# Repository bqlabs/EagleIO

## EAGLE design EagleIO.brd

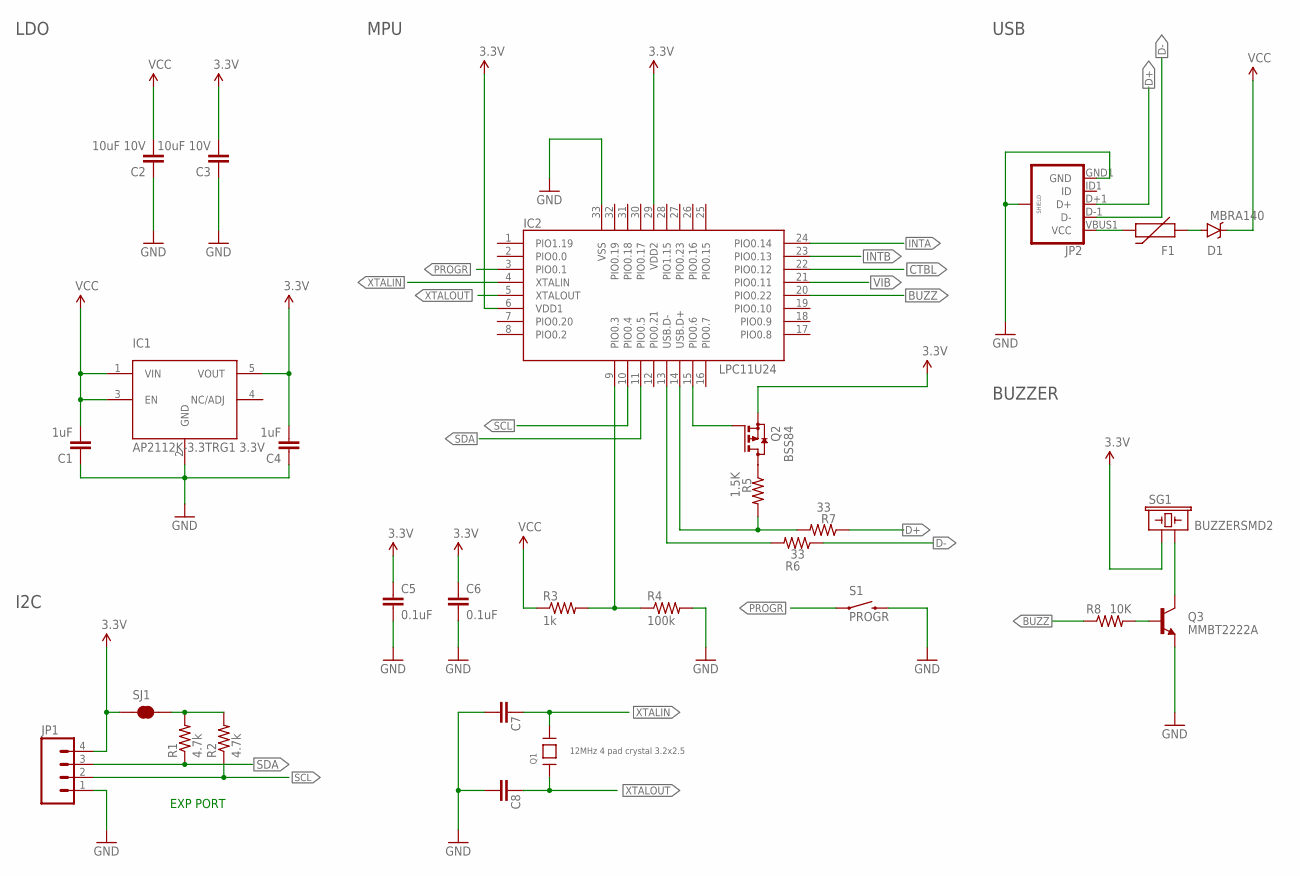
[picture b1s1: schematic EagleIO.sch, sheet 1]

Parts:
C1, C4: 1uF; 0402-CAP
C2, C3: 10uF 10V; 0402-CAP
C5, C6: 0.1uF; 0402-CAP
C7, C8: 27pF; 0402-CAP
D1: MBRA140; SMA-DIODE
F1: PTC0603; 0603
IC1: AP2112K-3.3TRG1 3.3V; SOT23-5
IC2: LPC11U24; HVQFN33_5X5MM
JP1: M04LONGPADS; 1X04_LONGPADS
JP2: USB_MICROB_PLUGCONN-11752; USB-B-MICRO-SMD_V03
Q1: 12MHz 4 pad crystal 3.2x2.5; CRYSTAL_3.2X2.5
Q2: BSS84; SOT23
Q3: MMBT2222A; SOT23-3
R1, R2: 4.7k; 0402-RES
R3: 1k; 0402-RES
R4: 100k; 0402-RES
R5: 1.5K; 0402-RES
R6, R7: 33; 0402-RES
R8: 10K; 0402-RES
S1: PROGR; TACTILE-SWITCH-1101NE
SG1: BUZZERSMD2; BUZZER-CCV
SJ1: JUMPER-PAD-2-NC_BY_TRACE; PAD-JUMPER-2-NC_BY_TRACE_YES_SILK

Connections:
3.3V: C3.2, C4.2, C5.1, C6.1, IC1.5 (VOUT), IC2.6 (VDD1), IC2.29 (VDD2), JP1.4, Q2.2 (S), SG1.+ (1), SJ1.1; also elsewhere on the board
BUZZ: IC2.20 (PIO0.22), R8.1
CTBL: IC2.22 (PIO0.12); also elsewhere on the board
D+: JP2.D+1 (D+), R7.1
D-: JP2.D-1 (D-), R6.1
GND: C1.1, C2.1, C3.1, C4.1, C5.2, C6.2, C7.2, C8.2, IC1.2 (GND), IC2.33 (VSS), JP1.1, JP2.GND1 (GND), JP2.SHIELD1 (SHIELD), JP2.SHIELD2 (SHIELD), JP2.SHIELD3 (SHIELD), Q3.2 (E), R4.2, S1.2; also elsewhere on the board
INTA: IC2.24 (PIO0.14); also elsewhere on the board
INTB: IC2.23 (PIO0.13); also elsewhere on the board
unnamed: D1.A, F1.1
unnamed: F1.2, JP2.VBUS1 (VCC)
unnamed: Q3.3 (C), SG1.- (2)
unnamed: Q3.1 (B), R8.2
unnamed: IC2.14 (USB.D+), R5.2, R7.2
unnamed: IC2.13 (USB.D-), R6.2
unnamed: Q2.3 (D), R5.1
unnamed: IC2.15 (PIO0.6), Q2.1 (G)
unnamed: R1.2, R2.2, SJ1.2
P0.3/ISP_COMMAND_USB_HIGH: IC2.9 (PIO0.3), R3.2, R4.1
PROGR: IC2.3 (PIO0.1), S1.1
SCL: IC2.10 (PIO0.4), JP1.2, R2.1; also elsewhere on the board
SDA: IC2.11 (PIO0.5), JP1.3, R1.1; also elsewhere on the board
VCC: C1.2, C2.2, D1.C, IC1.1 (VIN), IC1.3 (EN), R3.1; also elsewhere on the board
VIB: IC2.21 (PIO0.11); also elsewhere on the board
XTALIN: C7.1, IC2.4 (XTALIN), Q1.3
XTALOUT: C8.1, IC2.5 (XTALOUT), Q1.1

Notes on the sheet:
LDO
MPU
USB
I2C
BUZZER
EXP PORT

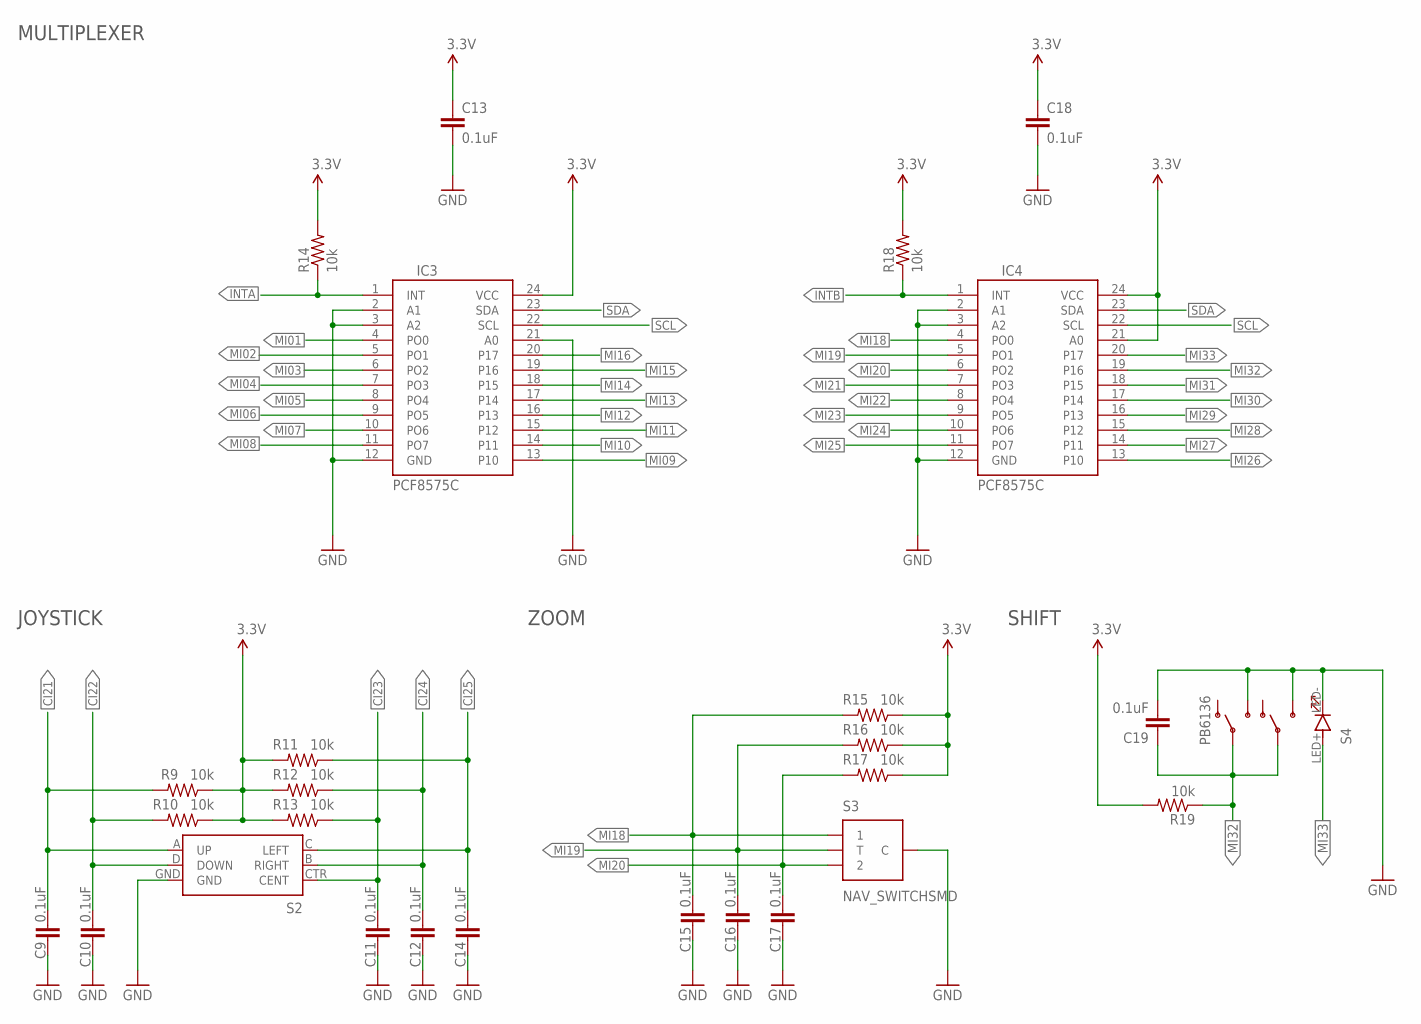
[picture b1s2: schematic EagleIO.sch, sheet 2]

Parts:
C9, C10, C11, C12, C13, C14, C15, C16, C17, C18, C19: 0.1uF; 0402-CAP
IC3, IC4: PCF8575C; SO-24DW
R9, R10, R11, R12, R13, R14, R15, R16, R17, R18, R19: 10k; 0402-RES
S2: JOYSTICK_MINI
S3: NAV_SWITCHSMD; NAV_SWITCH
S4: PB6136

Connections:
3.3V: C13.1, C18.1, IC3.24 (VCC), IC4.21 (A0), IC4.24 (VCC), R9.1, R10.1, R11.2, R12.2, R13.2, R14.2, R15.1, R16.1, R17.1, R18.2, R19.2; also elsewhere on the board
CI21: C9.2, R9.2, S2.A (UP); also elsewhere on the board
CI22: C10.2, R10.2, S2.D (DOWN); also elsewhere on the board
CI23: C11.2, R13.1, S2.CTR (CENT); also elsewhere on the board
CI24: C12.2, R12.1, S2.B (RIGHT); also elsewhere on the board
CI25: C14.2, R11.1, S2.C (LEFT); also elsewhere on the board
GND: C9.1, C10.1, C11.1, C12.1, C13.2, C14.1, C15.1, C16.1, C17.1, C18.2, C19.2, IC3.2 (A1), IC3.3 (A2), IC3.12 (GND), IC3.21 (A0), IC4.2 (A1), IC4.3 (A2), IC4.12 (GND), S2.GND, S3.C, S4.LED- (2), S4.NO1 (S), S4.NO2 (S1); also elsewhere on the board
INTA: IC3.1 (INT), R14.1; also elsewhere on the board
INTB: IC4.1 (INT), R18.1; also elsewhere on the board
MI01: IC3.4 (PO0); also elsewhere on the board
MI02: IC3.5 (PO1); also elsewhere on the board
MI03: IC3.6 (PO2); also elsewhere on the board
MI04: IC3.7 (PO3); also elsewhere on the board
MI05: IC3.8 (PO4); also elsewhere on the board
MI06: IC3.9 (PO5); also elsewhere on the board
MI07: IC3.10 (PO6); also elsewhere on the board
MI08: IC3.11 (PO7); also elsewhere on the board
MI09: IC3.13 (P10); also elsewhere on the board
MI10: IC3.14 (P11); also elsewhere on the board
MI11: IC3.15 (P12); also elsewhere on the board
MI12: IC3.16 (P13); also elsewhere on the board
MI13: IC3.17 (P14); also elsewhere on the board
MI14: IC3.18 (P15); also elsewhere on the board
MI15: IC3.19 (P16)
MI16: IC3.20 (P17)
MI18: C15.2, IC4.4 (PO0), R15.2, S3.1
MI19: C16.2, IC4.5 (PO1), R16.2, S3.T
MI20: C17.2, IC4.6 (PO2), R17.2, S3.2
MI21: IC4.7 (PO3); also elsewhere on the board
MI22: IC4.8 (PO4); also elsewhere on the board
MI23: IC4.9 (PO5); also elsewhere on the board
MI24: IC4.10 (PO6); also elsewhere on the board
MI25: IC4.11 (PO7); also elsewhere on the board
MI26: IC4.13 (P10); also elsewhere on the board
MI27: IC4.14 (P11); also elsewhere on the board
MI28: IC4.15 (P12); also elsewhere on the board
MI29: IC4.16 (P13)
MI30: IC4.17 (P14)
MI31: IC4.18 (P15)
MI32: C19.1, IC4.19 (P16), R19.1, S4.C1, S4.C2 (P1)
MI33: IC4.20 (P17), S4.LED+ (1)
SCL: IC3.22 (SCL), IC4.22 (SCL); also elsewhere on the board
SDA: IC3.23 (SDA), IC4.23 (SDA); also elsewhere on the board

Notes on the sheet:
MULTIPLEXER
JOYSTICK
ZOOM
SHIFT

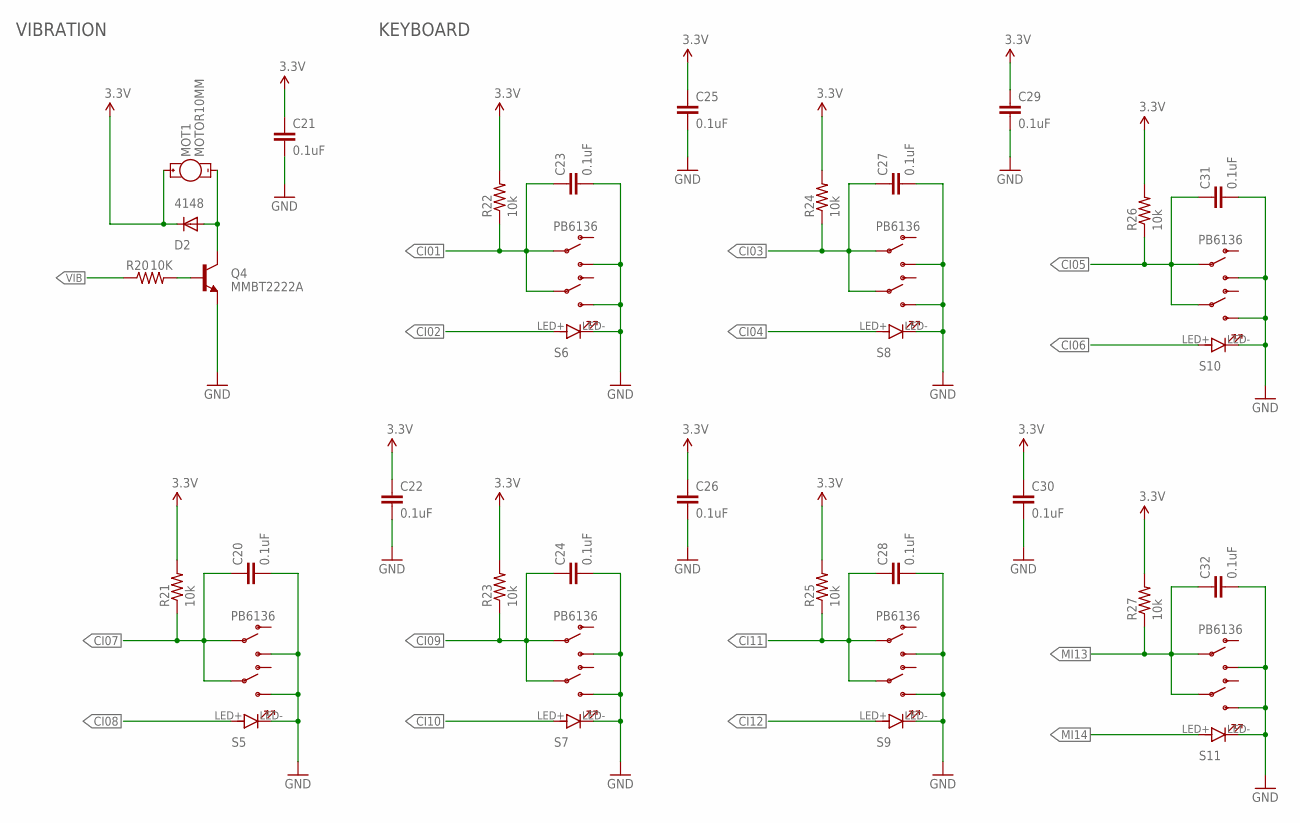
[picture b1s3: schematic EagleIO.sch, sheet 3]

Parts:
C20, C21, C22, C23, C24, C25, C26, C27, C28, C29, C30, C31, C32: 0.1uF; 0402-CAP
D2: 4148; MINIMELF
MOT1: MOTOR10MM; VIBE-MOTOR-10MM
Q4: MMBT2222A; SOT23-3
R20: 10K; 0402-RES
R21, R22, R23, R24, R25, R26, R27: 10k; 0402-RES
S5, S6, S7, S8, S9, S10, S11: PB6136

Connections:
3.3V: C21.1, C22.1, C25.1, C26.1, C29.1, C30.1, D2.C, MOT1.+, R21.2, R22.2, R23.2, R24.2, R25.2, R26.2, R27.2; also elsewhere on the board
CI01: C23.1, R22.1, S6.C1, S6.C2 (P1); also elsewhere on the board
CI02: S6.LED+ (1); also elsewhere on the board
CI03: C27.1, R24.1, S8.C1, S8.C2 (P1); also elsewhere on the board
CI04: S8.LED+ (1); also elsewhere on the board
CI05: C31.1, R26.1, S10.C1, S10.C2 (P1); also elsewhere on the board
CI06: S10.LED+ (1); also elsewhere on the board
CI07: C20.1, R21.1, S5.C1, S5.C2 (P1); also elsewhere on the board
CI08: S5.LED+ (1); also elsewhere on the board
CI09: C24.1, R23.1, S7.C1, S7.C2 (P1); also elsewhere on the board
CI10: S7.LED+ (1); also elsewhere on the board
CI11: C28.1, R25.1, S9.C1, S9.C2 (P1); also elsewhere on the board
CI12: S9.LED+ (1); also elsewhere on the board
GND: C20.2, C21.2, C22.2, C23.2, C24.2, C25.2, C26.2, C27.2, C28.2, C29.2, C30.2, C31.2, C32.2, Q4.2 (E), S5.LED- (2), S5.NO1 (S), S5.NO2 (S1), S6.LED- (2), S6.NO1 (S), S6.NO2 (S1), S7.LED- (2), S7.NO1 (S), S7.NO2 (S1), S8.LED- (2), S8.NO1 (S), S8.NO2 (S1), S9.LED- (2), S9.NO1 (S), S9.NO2 (S1), S10.LED- (2), S10.NO1 (S), S10.NO2 (S1), S11.LED- (2), S11.NO1 (S), S11.NO2 (S1); also elsewhere on the board
MI13: C32.1, R27.1, S11.C1, S11.C2 (P1); also elsewhere on the board
MI14: S11.LED+ (1); also elsewhere on the board
unnamed: D2.A, MOT1.-, Q4.3 (C)
unnamed: Q4.1 (B), R20.2
VIB: R20.1; also elsewhere on the board

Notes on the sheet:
VIBRATION
KEYBOARD

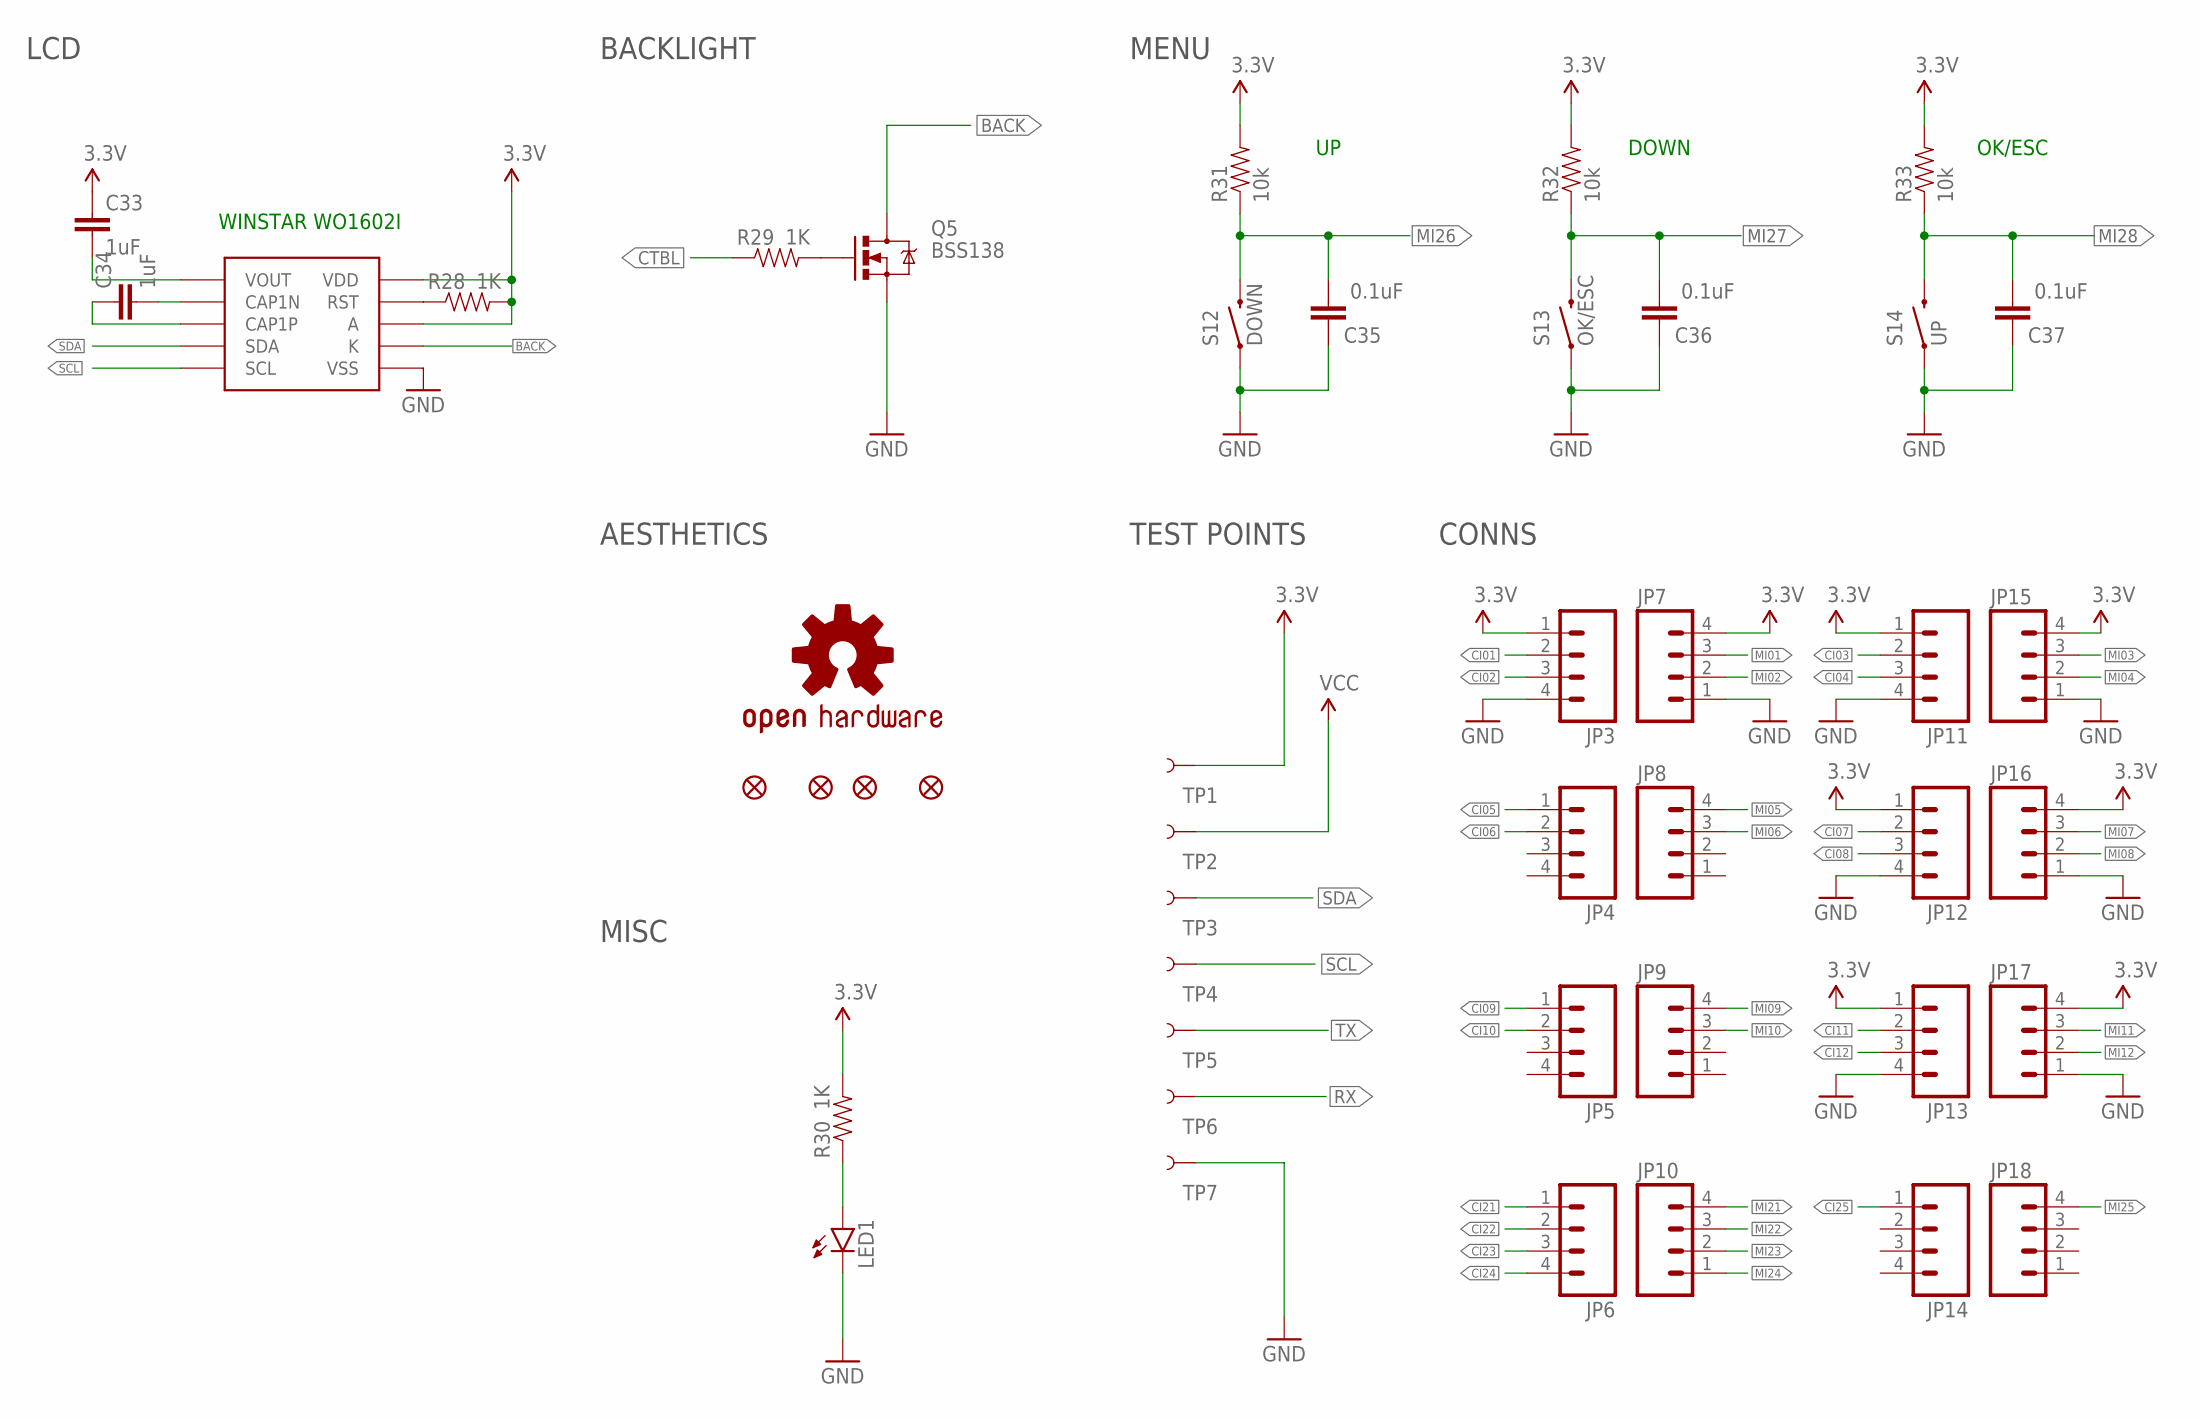
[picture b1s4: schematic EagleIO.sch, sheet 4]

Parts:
C33, C34: 1uF; 0402-CAP
C35, C36, C37: 0.1uF; 0402-CAP
FID1, FID2, FID3, FID4: FIDUCIAL1X2; FIDUCIAL-1X2
JP3, JP4, JP5, JP6, JP7, JP8, JP9, JP10, JP11, JP12, JP13, JP14, JP15, JP16, JP17, JP18: M041.27MM; 1X04-1.27MM
LCD1: WINSTAR_WO1602I
LED1: LED0603; LED-0603
LOGO1: OSHW-LOGOS; OSHW-LOGO-S
Q5: BSS138; SOT323
R28, R29, R30: 1K; 0402-RES
R31, R32, R33: 10k; 0402-RES
S12: DOWN; TACTILE-SWITCH-1101NE
S13: OK/ESC; TACTILE-SWITCH-1101NE
S14: UP; TACTILE-SWITCH-1101NE
TP1, TP2, TP3, TP4, TP5, TP6, TP7: TEST-POINT3X5; PAD.03X.05

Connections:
3.3V: C33.1, JP3.1, JP7.4, JP11.1, JP12.1, JP13.1, JP15.4, JP16.4, JP17.4, LCD1.AB (A), LCD1.AT (A), LCD1.VDD, R28.2, R30.2, R31.2, R32.2, R33.2, TP1.P$1; also elsewhere on the board
BACK: LCD1.KB (K), LCD1.KT (K), Q5.3 (D)
CI01: JP3.2; also elsewhere on the board
CI02: JP3.3; also elsewhere on the board
CI03: JP11.2; also elsewhere on the board
CI04: JP11.3; also elsewhere on the board
CI05: JP4.1; also elsewhere on the board
CI06: JP4.2; also elsewhere on the board
CI07: JP12.2; also elsewhere on the board
CI08: JP12.3; also elsewhere on the board
CI09: JP5.1; also elsewhere on the board
CI10: JP5.2; also elsewhere on the board
CI11: JP13.2; also elsewhere on the board
CI12: JP13.3; also elsewhere on the board
CI21: JP6.1; also elsewhere on the board
CI22: JP6.2; also elsewhere on the board
CI23: JP6.3; also elsewhere on the board
CI24: JP6.4; also elsewhere on the board
CI25: JP14.1; also elsewhere on the board
CTBL: R29.1; also elsewhere on the board
GND: C35.1, C36.1, C37.1, JP3.4, JP7.1, JP11.4, JP12.4, JP13.4, JP15.1, JP16.1, JP17.1, LCD1.VSS, LED1.C, Q5.2 (S), S12.1, S13.1, S14.1, TP7.P$1; also elsewhere on the board
MI01: JP7.3; also elsewhere on the board
MI02: JP7.2; also elsewhere on the board
MI03: JP15.3; also elsewhere on the board
MI04: JP15.2; also elsewhere on the board
MI05: JP8.4; also elsewhere on the board
MI06: JP8.3; also elsewhere on the board
MI07: JP16.3; also elsewhere on the board
MI08: JP16.2; also elsewhere on the board
MI09: JP9.4; also elsewhere on the board
MI10: JP9.3; also elsewhere on the board
MI11: JP17.3; also elsewhere on the board
MI12: JP17.2; also elsewhere on the board
MI21: JP10.4; also elsewhere on the board
MI22: JP10.3; also elsewhere on the board
MI23: JP10.2; also elsewhere on the board
MI24: JP10.1; also elsewhere on the board
MI25: JP18.4; also elsewhere on the board
MI26: C35.2, R31.1, S12.2; also elsewhere on the board
MI27: C36.2, R32.1, S13.2; also elsewhere on the board
MI28: C37.2, R33.1, S14.2; also elsewhere on the board
unnamed: Q5.1 (G), R29.2
unnamed: LED1.A, R30.1
unnamed: C33.2, LCD1.VOUT
unnamed: LCD1.RST, R28.1
unnamed: C34.2, LCD1.CAPN (CAP1N)
unnamed: C34.1, LCD1.CAP1P
RX: TP6.P$1
SCL: LCD1.SCL, TP4.P$1; also elsewhere on the board
SDA: LCD1.SDA, TP3.P$1; also elsewhere on the board
TX: TP5.P$1
VCC: TP2.P$1; also elsewhere on the board

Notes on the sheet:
LCD
WINSTAR WO1602I
BACKLIGHT
MENU
DOWN
OK/ESC
AESTHETICS
TEST POINTS
MISC
CONNS

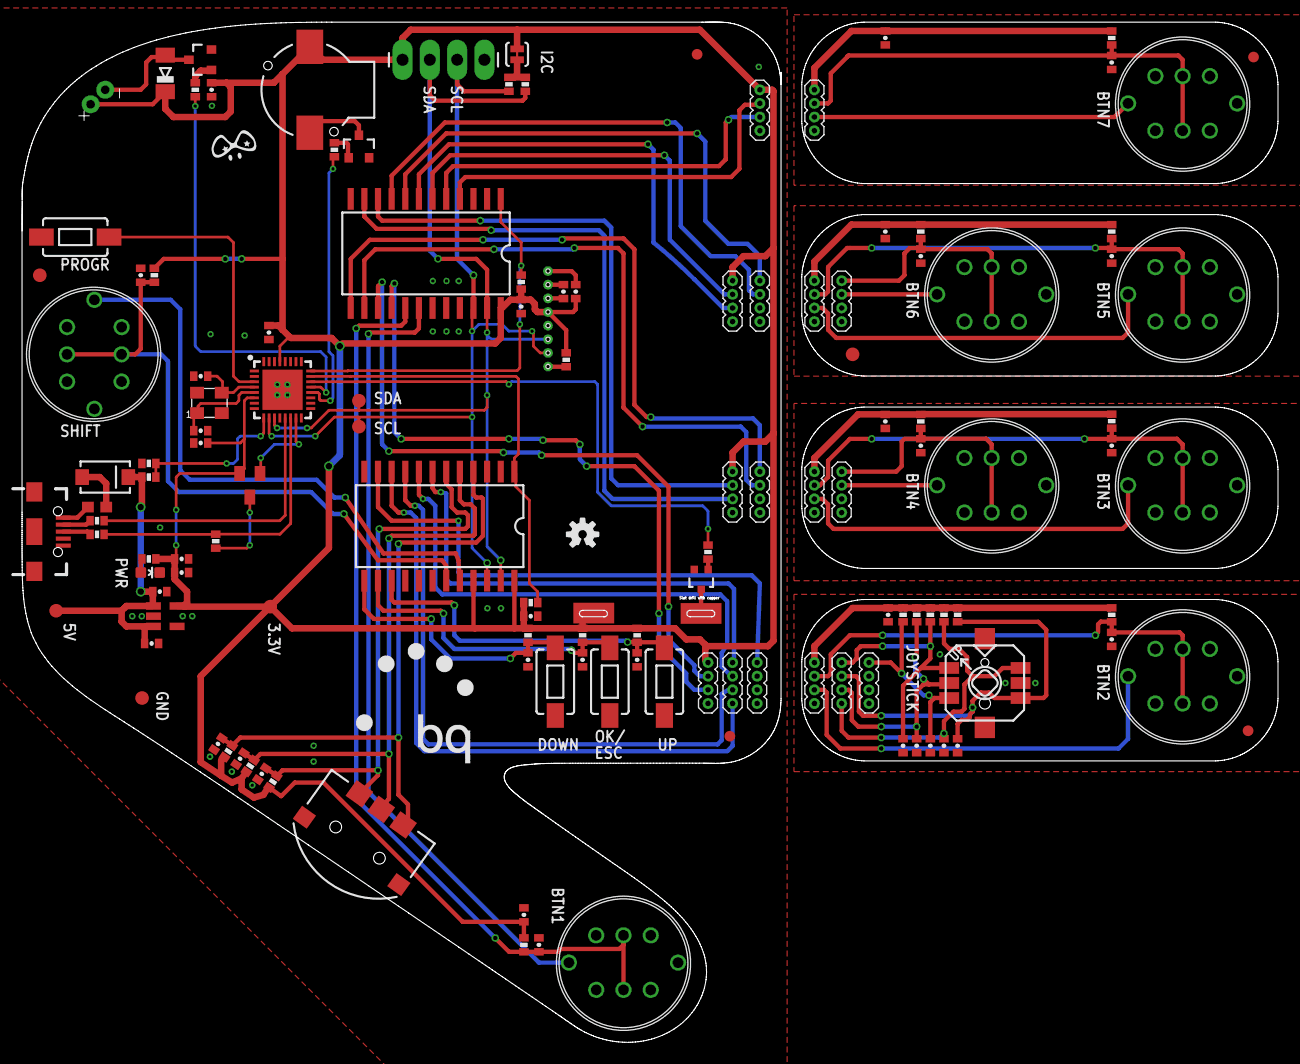
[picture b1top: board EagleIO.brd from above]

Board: 2 copper layers, 117.0 x 95.0 mm, 133 parts (0 on the bottom side), 78 nets.

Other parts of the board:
U$1: BQ_LOGO
U$2: PIGHIXXX_LOGO

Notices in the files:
parts and their libraries:
SparkFun-Passives: Licensing: Creative Commons ShareAlike 4.0 International - https://creativecommons.org/licenses/by-sa/4.0
SparkFun-PowerIC: Licensing: CC v3.0 Share-Alike You are welcome to use this library for commercial purposes.
